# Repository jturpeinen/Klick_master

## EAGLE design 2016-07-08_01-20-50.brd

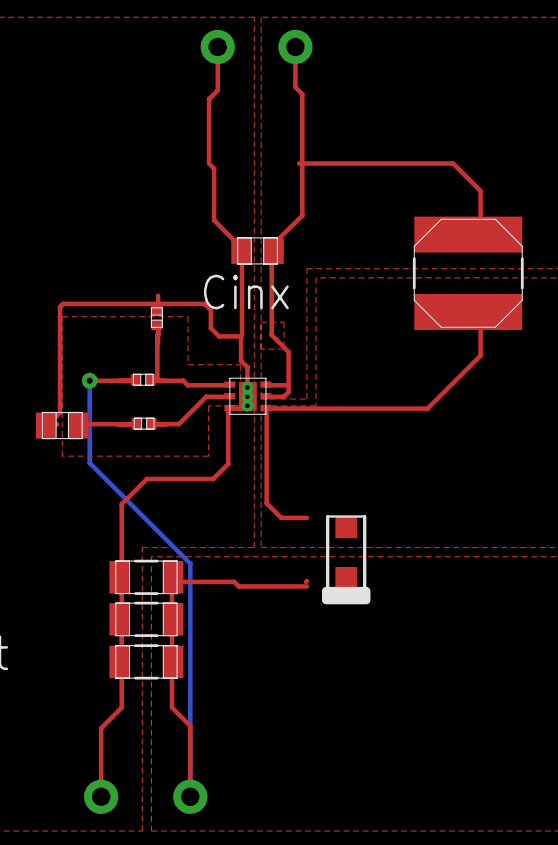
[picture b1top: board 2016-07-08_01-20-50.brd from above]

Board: 4 copper layers, 15 parts (0 on the bottom side), 7 nets.

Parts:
Ccomp: 0805
Cin: 0805
Cout_1, Cout_2, Cout_3: 1206
D1: SOD-123F
GND, GND1: TP-1502
L1: SRN6045
Rcomp: 0402
Rfbb: 0402
Rfbt: 0402
U1: S-PWSON-N6
VIN: TP-1502
VOUT: TP-1502

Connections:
0: Ccomp.2, Cin.2, Cout_1.2, Cout_2.2, Cout_3.2, GND.1, GND1.1, Rfbb.2, U1.3, U1.7
1: Ccomp.1, Rcomp.1
2: Cin.1, L1.1, U1.5, U1.6, VIN.1
3: Rfbb.1, Rfbt.2, U1.1
4: Cout_1.1, Cout_2.1, Cout_3.1, D1.1, Rfbt.1, VOUT.1
7: D1.2, L1.2, U1.4
8: Rcomp.2, U1.2

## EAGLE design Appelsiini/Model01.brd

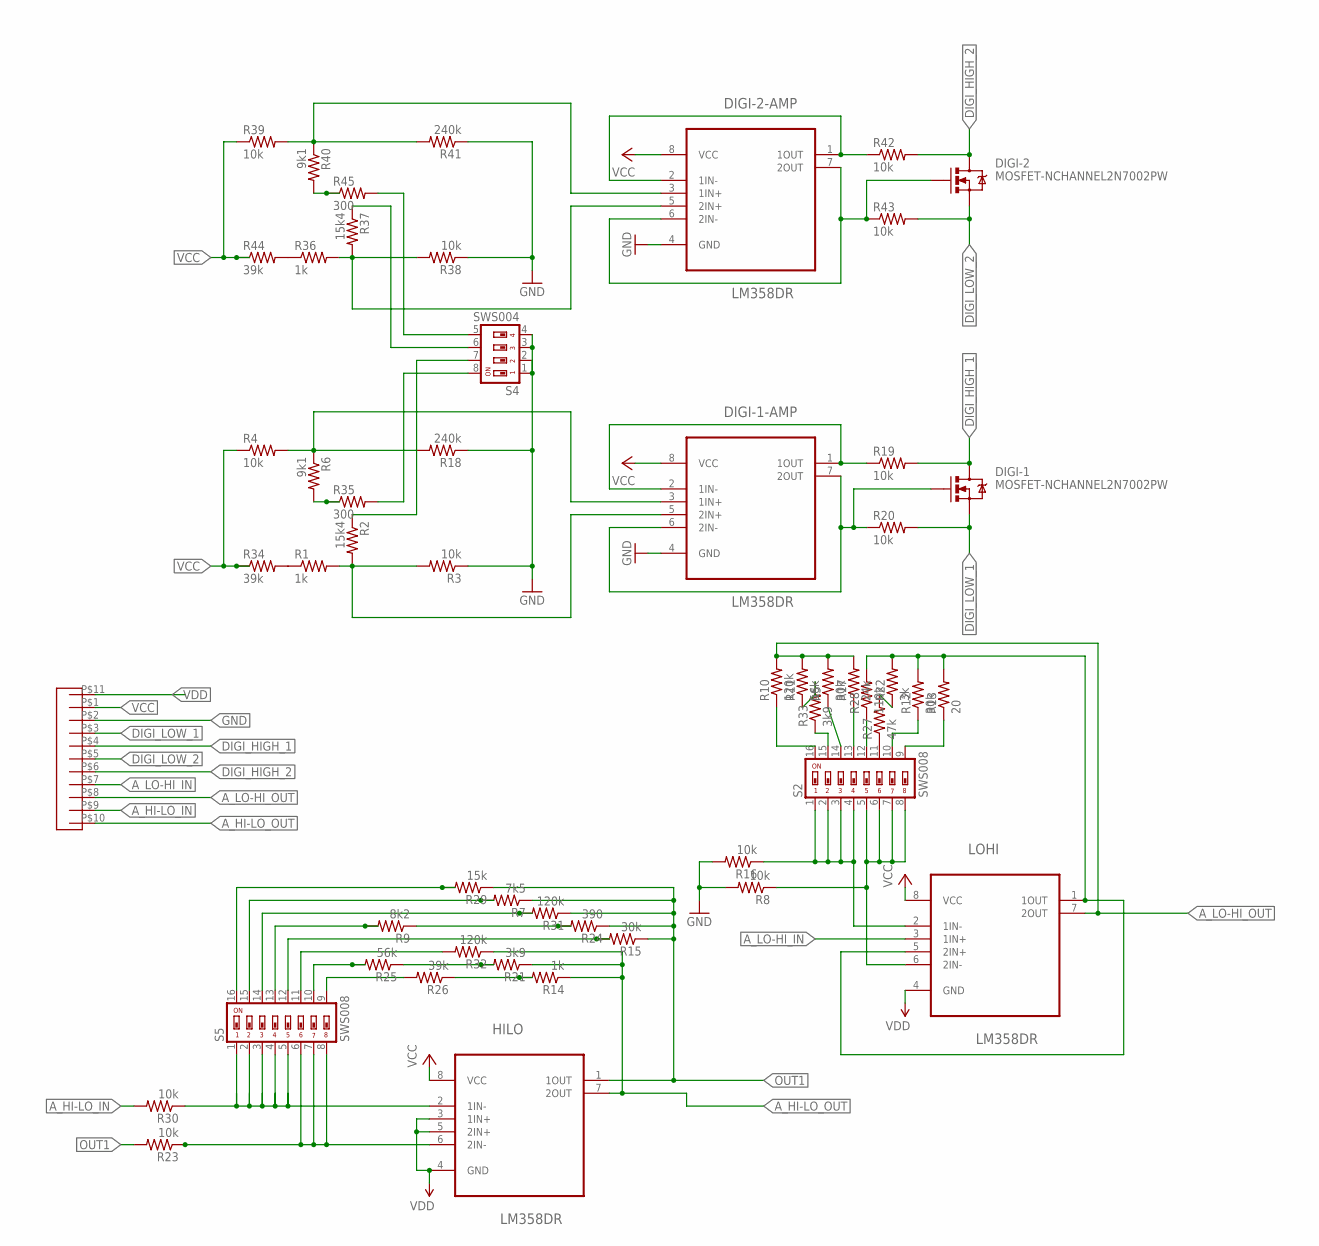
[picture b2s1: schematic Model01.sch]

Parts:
DIGI-1, DIGI-2: MOSFET-NCHANNEL2N7002PW; SOT323
DIGI-1-AMP, DIGI-2-AMP: LM358DR; SOIC127P600X175-8N
HILO: LM358DR; SOIC127P600X175-8N
LOHI: LM358DR; SOIC127P600X175-8N
R1, R14, R36: 1k; R0805
R2, R37: 15k4; R0805
R3, R4, R8, R16, R19, R20, R23, R30, R38, R39, R42, R43: 10k; R0805
R5, R12, R15: 30k; R0805
R6, R40: 9k1; R0805
R7: 7k5; R0805
R9: 8k2; R0805
R10, R31, R32: 120k; R0805
R11, R25: 56k; R0805
R13: 20; R0805
R17: 24k; R0805
R18, R41: 240k; R0805
R21, R33: 3k9; R0805
R22: 3k; R0805
R24: 390; R0805
R26, R34, R44: 39k; R0805
R27: 47k; R0805
R28: 110k; R0805
R29: 15k; R0805
R35, R45: 300; R0805
S2, S5: SWS008; SMS-008
S4: SWS004; SMS-004
U$1: 5.08PITCHTERMINAL; 10KPL508

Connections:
A_HI-LO_IN: R30.2, U$1.P$9
A_HI-LO_OUT: HILO.7 (2OUT), R14.1, R21.1, R32.1, U$1.P$10
A_LO-HI_IN: LOHI.3 (1IN+), U$1.P$7
A_LO-HI_OUT: LOHI.7 (2OUT), R5.2, R10.2, R11.2, R17.2, U$1.P$8
DI-1: DIGI-1-AMP.1 (1OUT), DIGI-1-AMP.2 (1IN-), R19.1
DIGI_HIGH_1: DIGI-1.3 (D), R19.2, U$1.P$4
DIGI_HIGH_2: DIGI-2.3 (D), R42.2, U$1.P$6
DIGI_LOW_1: DIGI-1.2 (S), R20.2, U$1.P$3
DIGI_LOW_2: DIGI-2.2 (S), R43.2, U$1.P$5
GND: DIGI-1-AMP.4 (GND), DIGI-2-AMP.4 (GND), R3.1, R8.2, R16.2, R18.1, R38.1, R41.1, S4.1, S4.2, S4.3, S4.4, U$1.P$2
unnamed: DIGI-1-AMP.3 (1IN+), R4.2, R6.1, R18.2
unnamed: R2.1, S4.7
unnamed: R6.2, R35.1
unnamed: DIGI-1-AMP.5 (2IN+), R1.2, R2.2, R3.2
unnamed: DIGI-1.1 (G), DIGI-1-AMP.6 (2IN-), DIGI-1-AMP.7 (2OUT), R20.1
unnamed: DIGI-2-AMP.5 (2IN+), R36.2, R37.2, R38.2
unnamed: HILO.2 (1IN-), R30.1, S5.1, S5.2, S5.3, S5.4, S5.5
unnamed: DIGI-2-AMP.3 (1IN+), R39.2, R40.1, R41.2
unnamed: R10.1, S2.16
unnamed: R33.1, S2.15
unnamed: R1.1, R34.2
unnamed: R5.1, S2.14
unnamed: R17.1, S2.13
unnamed: R28.1, S2.12
unnamed: R27.1, S2.11
unnamed: R12.1, S2.10
unnamed: R13.1, S2.9
unnamed: R29.2, S5.16
unnamed: LOHI.1 (1OUT), LOHI.5 (2IN+), R12.2, R13.2, R22.2, R28.2
unnamed: R7.2, S5.15
unnamed: R31.2, S5.14
unnamed: R9.2, S5.13
unnamed: R15.2, S5.12
unnamed: R32.2, S5.11
unnamed: HILO.6 (2IN-), R23.1, S5.6, S5.7, S5.8
unnamed: R25.2, S5.10
unnamed: R26.2, S5.9
unnamed: R14.2, R26.1
unnamed: R21.2, R25.1
unnamed: R9.1, R24.2
unnamed: R22.1, R27.2
unnamed: R11.1, R33.2
unnamed: R35.2, S4.8
unnamed: LOHI.2 (1IN-), R16.1, S2.1, S2.2, S2.3, S2.4
unnamed: LOHI.6 (2IN-), R8.1, S2.5, S2.6, S2.7, S2.8
unnamed: DIGI-2-AMP.1 (1OUT), DIGI-2-AMP.2 (1IN-), R42.1
unnamed: DIGI-2.1 (G), DIGI-2-AMP.6 (2IN-), DIGI-2-AMP.7 (2OUT), R43.1
unnamed: R37.1, S4.6
unnamed: R36.1, R44.2
unnamed: R40.2, R45.1
unnamed: R45.2, S4.5
OUT1: HILO.1 (1OUT), R7.1, R15.1, R23.2, R24.1, R29.1, R31.1
VCC: DIGI-1-AMP.8 (VCC), DIGI-2-AMP.8 (VCC), HILO.8 (VCC), LOHI.8 (VCC), R4.1, R34.1, R39.1, R44.1, U$1.P$1
VDD: HILO.3 (1IN+), HILO.4 (GND), HILO.5 (2IN+), LOHI.4 (GND), U$1.P$11

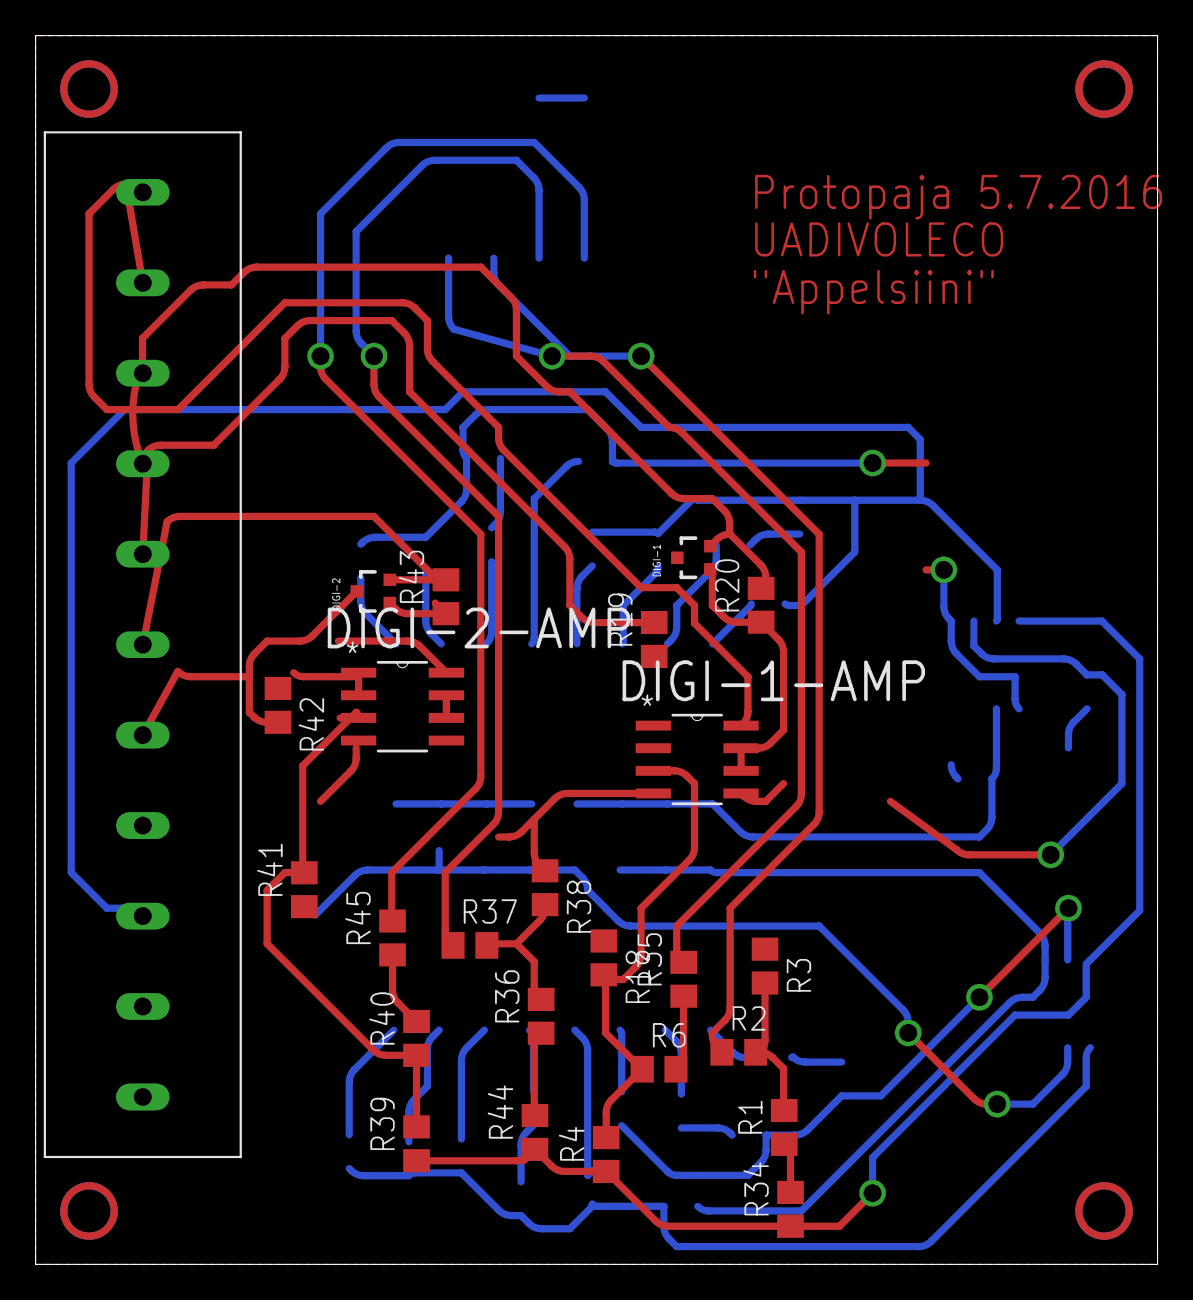
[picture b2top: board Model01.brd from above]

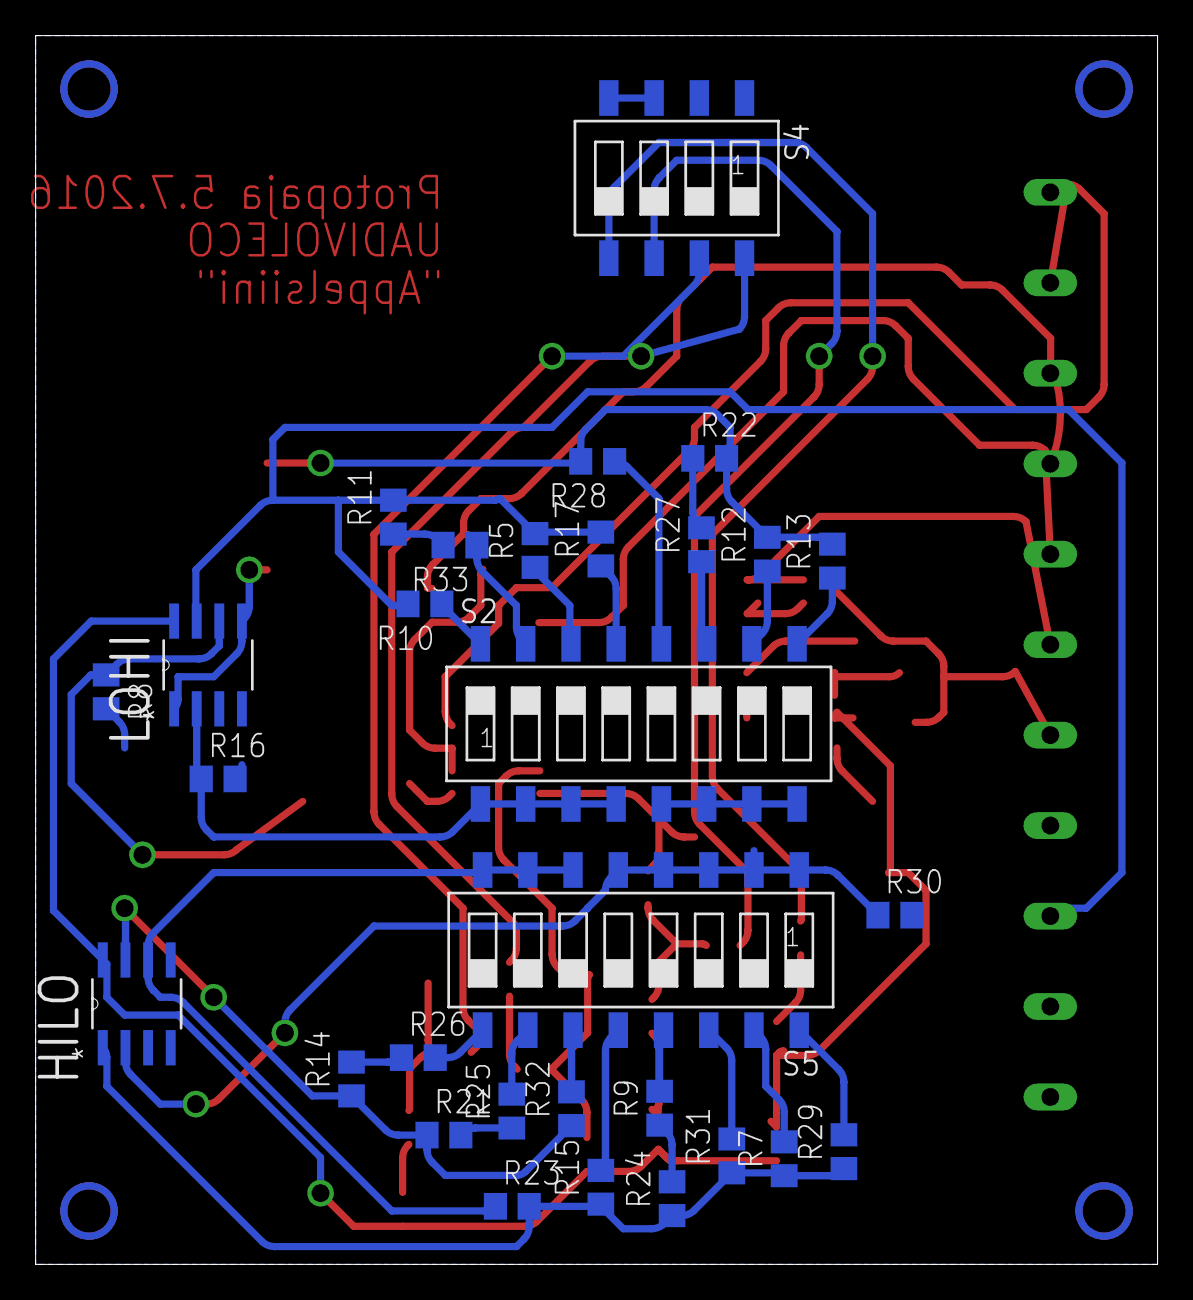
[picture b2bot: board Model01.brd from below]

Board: 2 copper layers, 63.0 x 69.0 mm, 55 parts (30 on the bottom side), 54 nets.

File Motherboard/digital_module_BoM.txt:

Partlist exported from C:/Users/PAJA/Documents/eagle/Uadi-voleco/Klick_master/Motherboard/digital_module.sch at 29.7.2016 13:46

Qty Value                   Device                  Package            Parts                  Description               MPN     OC_FARNELL OC_NEWARK PACKAGE PROD_ID     SUPPLIER         
4   10k                     R-US_R0805              R0805              R19, R20, R42, R43     RESISTOR, American symbol                                                                   
2   5.08PITCHTERMINAL       5.08PITCHTERMINAL       10KPL508           U$2, U$3                                                                                                           
2   LM358DR                 LM358DR                 SOIC127P600X175-8N DIGI-1-AMP, DIGI-2-AMP OPERATIONAL AMPLIFIERS    LM358DR 1831865    34K7599   SOIC-8              Texas Instruments
1   MODULE_CONNECTOR        MODULE_CONNECTOR        MODULE_CONNECTOR   U$1                                                                                                                
2   MOSFET-NCHANNEL2N7002PW MOSFET-NCHANNEL2N7002PW SOT323             DIGI-1, DIGI-2         Common NMOSFET Parts                                           TRANS-11151

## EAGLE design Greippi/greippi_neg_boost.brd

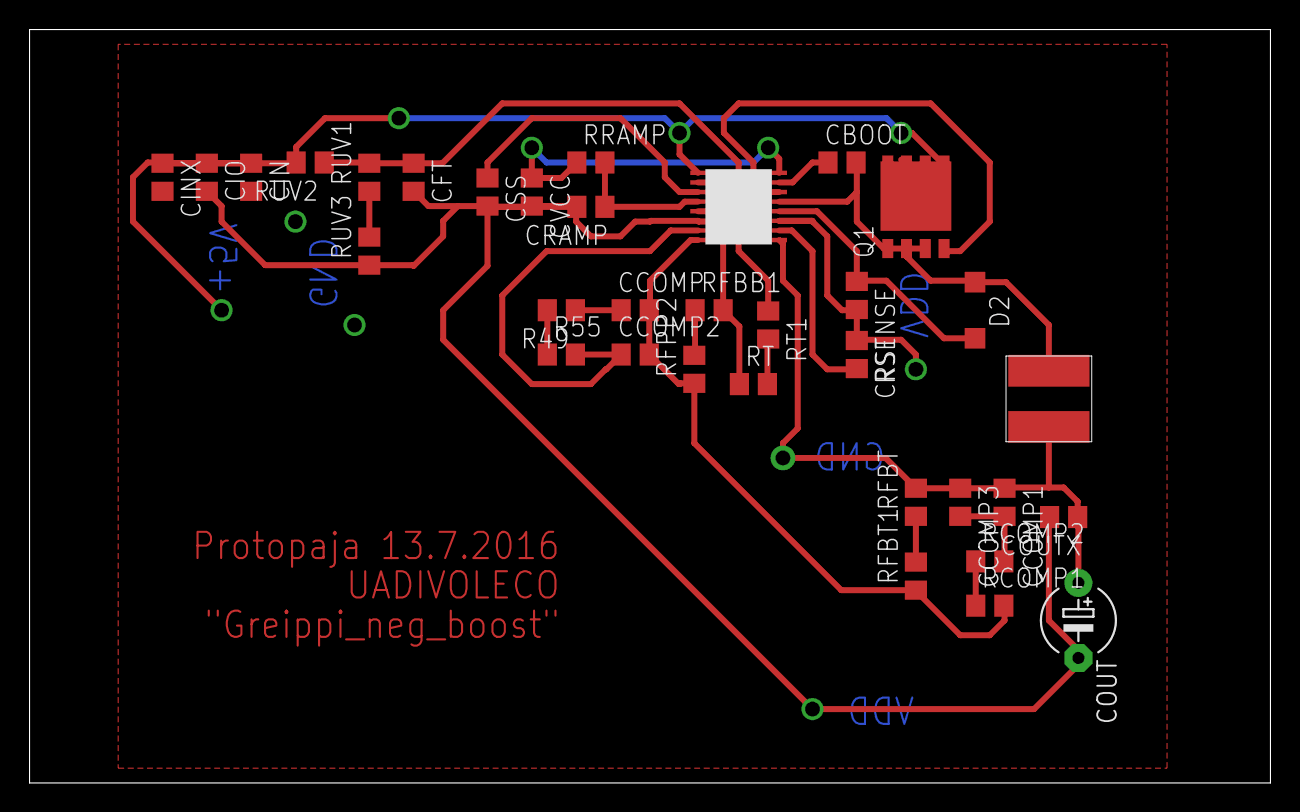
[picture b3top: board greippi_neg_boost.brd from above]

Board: 2 copper layers, 84.0 x 51.0 mm, 34 parts (0 on the bottom side), 23 nets.

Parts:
CBOOT: 100n; C0805
CCOMP: 56p; C0805
CCOMP1, CCOMP3: 150p; C0805
CCOMP2: 12p; C0805
CFT: 68n; C0805
CIN: 1uF; C0805
CINX: 100n; C0805
CIO: 1u; C0805
COUT: 22u; E5-5
COUTX: 1u; C0805
CRAMP: 180p; C0805
CRST: 22n; C0805
CSS: 56n; C0805
CVCC: 100n; C0805
D2: SOD123
Q1: BSZ105N04NS; PG-TDSON-8
R49: 5k6; R0805
R55: 220k; R0805
RCOMP1: 1k; R0805
RCOMP2: 6.8k; R0805
RFBB1: 1.5k; R0805
RFBT: 33k; R0805
RFBT1: 3k3; R0805
RFPP2: 150; R0805
RRAMP: 43k; R0805
RSENSE: 0.06; R0805
RT: 10k; R0805
RT1: 220; R0805
RUV1: 3.3k; R0805
RUV2: 10k; R0805
RUV3: 270; R0805
U$2: LM5088
U$3: KLICK_INDUCTOR01

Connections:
+5V: CIN.1, CINX.1, CIO.1, Q1.5, Q1.6, Q1.7, Q1.8, Q1.TH, RUV2.2, U$2.P$1
GND: CCOMP1.1, CCOMP3.1, CIN.2, CINX.2, COUT.+, COUTX.1, RFBT.2, U$2.P$16, U$3.P$1
unnamed: CFT.1, RUV1.2, RUV2.1, U$2.P$2
unnamed: CSS.1, U$2.P$3
unnamed: CVCC.1, RRAMP.1, U$2.P$9
unnamed: D2.A, RSENSE.1, U$2.P$13
unnamed: CRAMP.1, RRAMP.2, U$2.P$4
unnamed: RT.2, RT1.2
unnamed: RUV1.1, RUV3.2
unnamed: CCOMP.1, R49.1
unnamed: CCOMP.2, CCOMP2.2, RCOMP1.2, RFBT1.1, RFPP2.1, U$2.P$8
unnamed: CCOMP2.1, R55.2, U$2.P$7
unnamed: CBOOT.1, U$2.P$10
unnamed: CRST.2, U$2.P$15
unnamed: CBOOT.2, D2.C, Q1.1, Q1.2, Q1.3, U$2.P$12, U$3.P$2
unnamed: RFBB1.1, RFPP2.2
unnamed: Q1.4, U$2.P$11
unnamed: R49.2, R55.1
unnamed: CCOMP1.2, CCOMP3.2, RCOMP2.2
unnamed: RT1.1, U$2.P$5
unnamed: RCOMP1.1, RCOMP2.1
unnamed: RFBT.1, RFBT1.2
VDD: CFT.2, CIO.2, COUT.-, COUTX.2, CRAMP.2, CRST.1, CSS.2, CVCC.2, RFBB1.2, RSENSE.2, RT.1, RUV3.1, U$2.P$6, U$2.P$14

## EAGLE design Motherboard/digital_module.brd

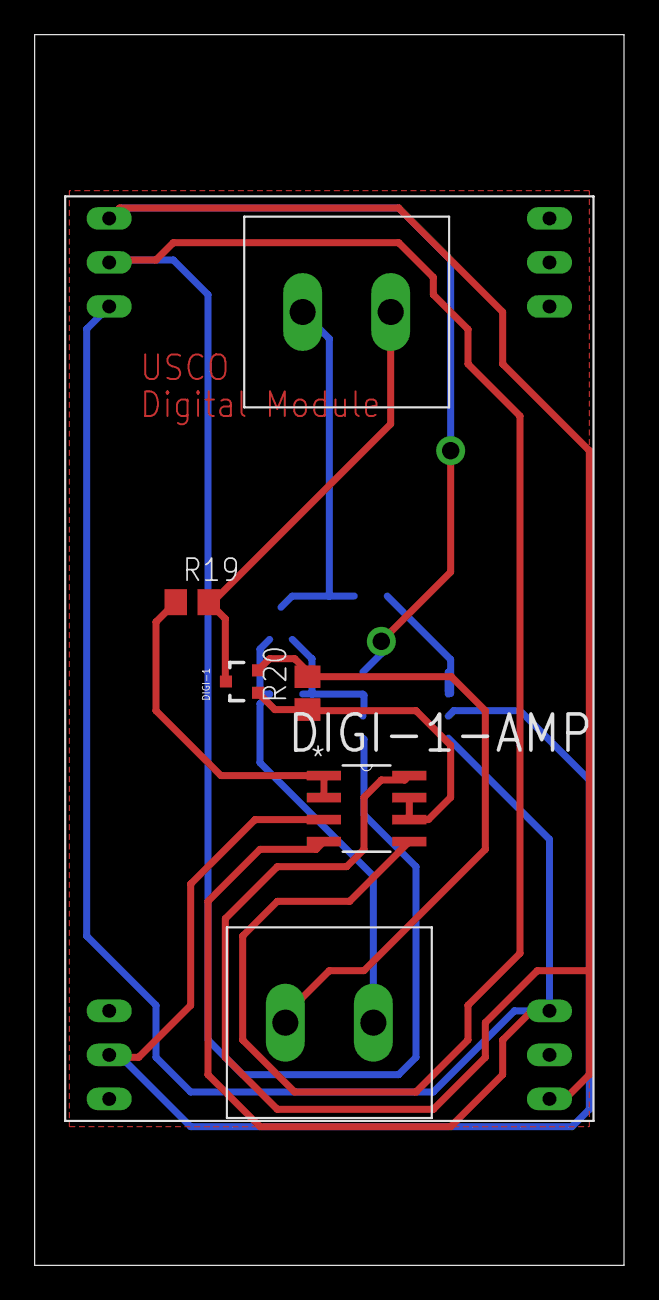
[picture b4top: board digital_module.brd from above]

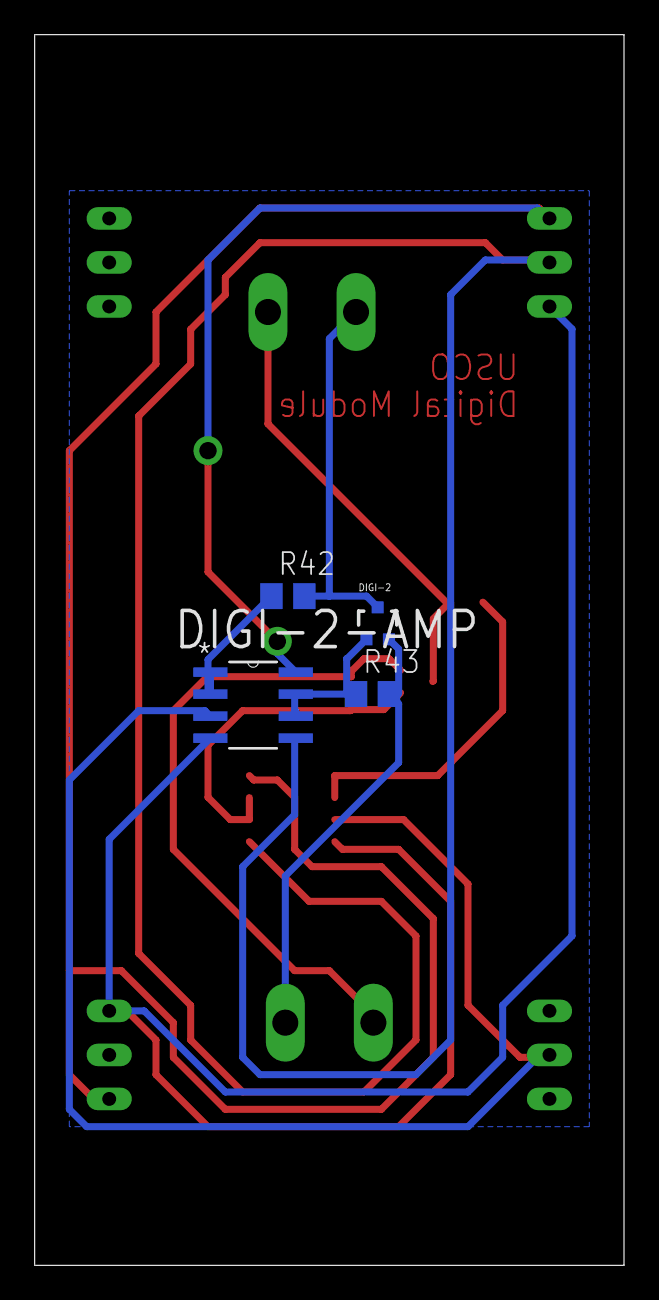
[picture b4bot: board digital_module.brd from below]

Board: 2 copper layers, 34.0 x 71.0 mm, 11 parts (4 on the bottom side), 12 nets.

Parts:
DIGI-1, DIGI-2: MOSFET-NCHANNEL2N7002PW; SOT323
DIGI-1-AMP, DIGI-2-AMP: LM358DR; SOIC127P600X175-8N
R19, R20, R42, R43: 10k; R0805
U$1: MODULE_CONNECTOR
U$2, U$3: 5.08PITCHTERMINAL; 10KPL508

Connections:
DI-1: DIGI-1-AMP.1, DIGI-1-AMP.2, R19.1
DIGI_HIGH_1: DIGI-1.3, R19.2, U$2.P$5
DIGI_HIGH_2: DIGI-2.3, R42.2, U$2.P$6
DIGI_HIGH_REF: DIGI-1-AMP.3, DIGI-2-AMP.3, U$1.P$2
DIGI_LOW_1: DIGI-1.2, R20.2, U$3.P$6
DIGI_LOW_2: DIGI-2.2, R43.2, U$3.P$5
DIGI_LOW_REF: DIGI-1-AMP.5, DIGI-2-AMP.5
GND: DIGI-1-AMP.4, DIGI-2-AMP.4, U$1.P$6, U$1.P$9
unnamed: DIGI-1.1, DIGI-1-AMP.6, DIGI-1-AMP.7, R20.1
unnamed: DIGI-2-AMP.1, DIGI-2-AMP.2, R42.1
unnamed: DIGI-2.1, DIGI-2-AMP.6, DIGI-2-AMP.7, R43.1
VCC: DIGI-1-AMP.8, DIGI-2-AMP.8, U$1.P$4, U$1.P$7

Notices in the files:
parts and their libraries:
SparkFun-DiscreteSemi: Licensing: Creative Commons ShareAlike 4.0 International - https://creativecommons.org/licenses/by-sa/4.0
